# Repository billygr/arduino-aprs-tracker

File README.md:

# arduino-aprs-tracker

Arduino APRS Tracker based on libAPRS with SmartBeaconing

## Hardware
* Arduino Pro Mini 3.3V 8 MHz https://www.adafruit.com/products/2377
* Adafruit Ultimate GPS https://www.adafruit.com/product/746
* or any GPS that can output NMEA (NEO-6M is tested with some minor issues)

## Libraries
* TinyGPS http://arduiniana.org/libraries/tinygps/
* libAPRS (modified) https://github.com/billygr/LibAPRS

## Notes
There are cases where the NEO-6M displays wrong data such as course/altitude. I have trace it to the interrupt of ADC (needed for APRS).
When the interrupt is fired, disrupts the SoftwareSerial so it looses GPS messages.
By default NEO-6M has these messages enabled GSV, RMC, GSA, GGA, GLL, VTG, TXT. 
The GLL is not needed so it is disabled on power on. If you still have issues enable the define, it will switch the NEO-6M on 4800 baud which looks like it fixes it

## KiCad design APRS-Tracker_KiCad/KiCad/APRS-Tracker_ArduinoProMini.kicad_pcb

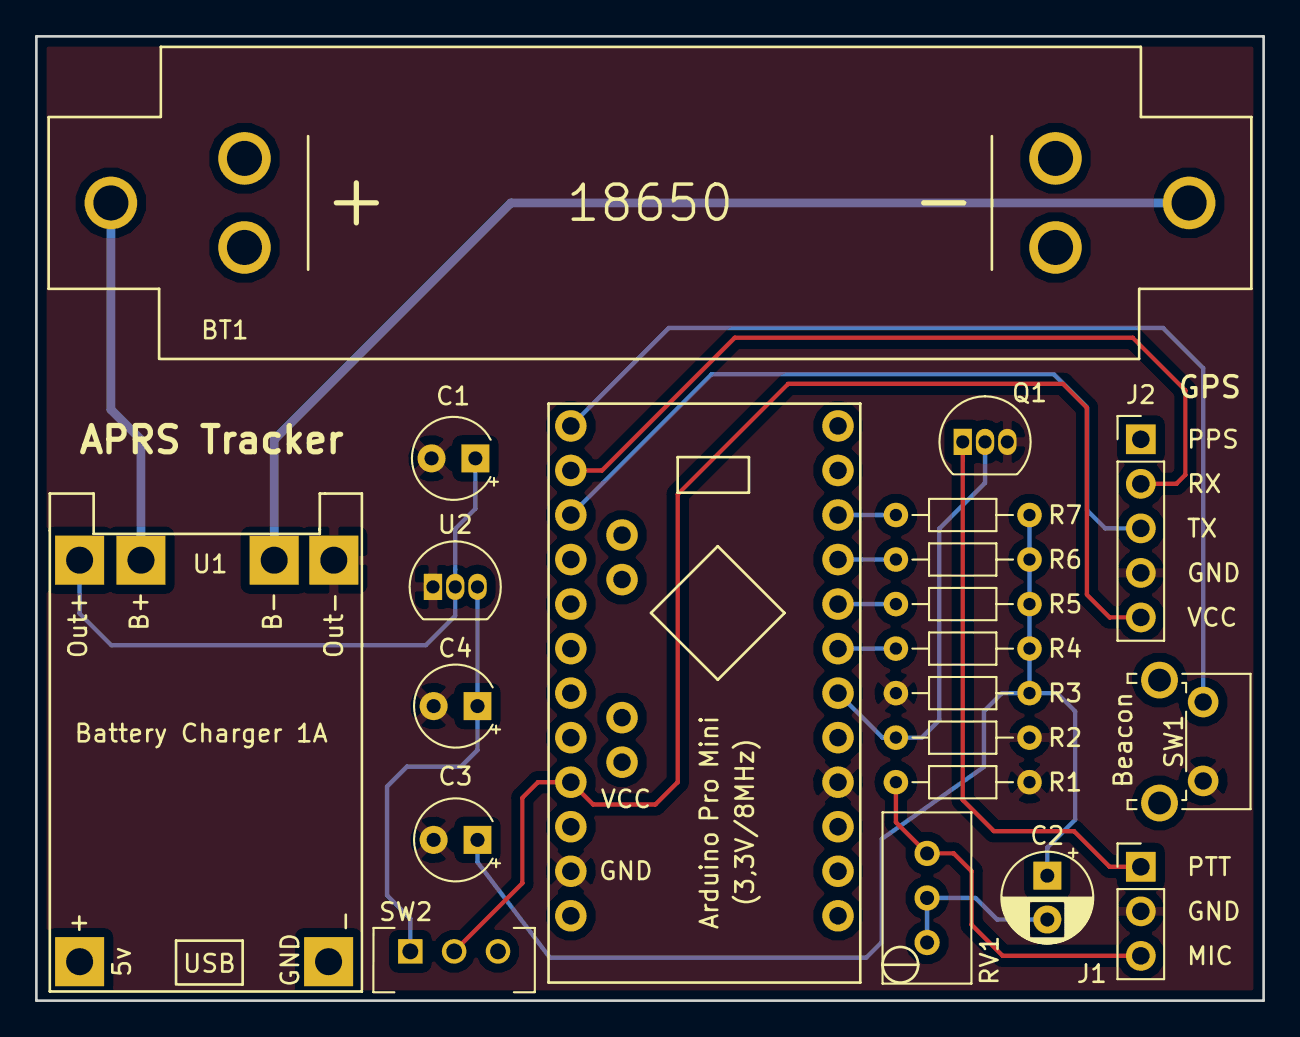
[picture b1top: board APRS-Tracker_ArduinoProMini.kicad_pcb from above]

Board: 2 copper layers, 70.0 x 55.0 mm, 21 parts (0 on the bottom side), 18 nets.

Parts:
BT1: Battery_Cell; Battery_ClipHolder_18650
C1, C4: 1uF; CP_Radial_Tantal_D4.5mm_P2.50mm
C2: 4,7uF/16V; CP_Radial_D5.0mm_P2.50mm
C3: 100nF; CP_Radial_Tantal_D4.5mm_P2.50mm
J1: Conn_01x03_Male; PinHeader_1x03_P2.54mm_Vertical
J2: Conn_01x05_Male; PinHeader_1x05_P2.54mm_Vertical
Q1: BS170; TO-92_Inline
R1, R7: 1k; R_Axial_DIN0204_L3.6mm_D1.6mm_P7.62mm_Horizontal
R2: 10k; R_Axial_DIN0204_L3.6mm_D1.6mm_P7.62mm_Horizontal
R3: 270; R_Axial_DIN0204_L3.6mm_D1.6mm_P7.62mm_Horizontal
R4: 8,2k; R_Axial_DIN0204_L3.6mm_D1.6mm_P7.62mm_Horizontal
R5: 3,9k; R_Axial_DIN0204_L3.6mm_D1.6mm_P7.62mm_Horizontal
R6: 2,2k; R_Axial_DIN0204_L3.6mm_D1.6mm_P7.62mm_Horizontal
RV1: 10k; Potentiometer_Bourns_3296W_Vertical
SW1: SW_Push; SW_Tactile_SPST_Angled_PTS645Vx31-2LFS
SW2: SW_SPDT; SW_CuK_JS202011BQN_SPDT_Angled
U1: TP4056; TP4056-18650
U2: MCP1700-3302E_TO92; TO-92_Inline
U3: Arduino-Pro-Mini; Arduino-ProMini

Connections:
+3V3: J2.5, SW2.2, U3.21
/MIC_ANALOG_OUT: J1.3, R1.2, RV1.3
/PTT: J1.1, Q1.1
/PTT_IN: Q1.2, R2.1, U3.6
/RX: J2.2, U3.14
/TX: J2.3, U3.15
GND: C1.2, C3.2, C4.2, J1.2, J2.4, Q1.3, R1.1, R2.2, R3.1, SW1.2, U1.4, U2.1, U3.4, U3.23
unnamed: BT1.1, U1.5
unnamed: BT1.2, U1.6
unnamed: C1.1, U1.3, U2.2
unnamed: C2.1, C3.1, R3.2, R4.2, R5.2, R6.2, R7.2
unnamed: C2.2, RV1.1, RV1.2
unnamed: C4.1, SW2.1, U2.3
unnamed: R4.1, U3.7
unnamed: R5.1, U3.8
unnamed: R6.1, U3.9
unnamed: R7.1, U3.10
unnamed: SW1.1, U3.13

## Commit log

2016-12-24 Import working version to git
2017-04-03 Fixes aprs conversion for negative lat/long
2017-08-15 Possible fix for wrong APRS icon
2017-11-13 Fix some warnings
2017-12-28 Fix for 3 digit lattitude
2018-07-08 Add configuration for the platformio build system.
2019-04-14 KiCad & Gerber Files for PCB
2019-04-16 Pictures added
2019-04-16 Pic size small
2019-09-19 Moved the ino under a folder to fix issues with travis
2019-12-31 Small updates, doc, indentation
2020-01-05 Fix warnings
    Use %lu for unsigned long variables.
2020-01-12 Added GPS fix led on A3 pin
2020-01-12 Added the SimpleTimer to the project from commit b30890b8f7046bf3b0258e5870e5dda78ac5c71a since the Arduino Library manager contains a complete different project/version
2020-01-12 Use the buidin SimpleTimer
2020-04-20 Added altitude in comment section of APRS messsage
2020-04-20 fix typo
2020-04-20 ... hopefully right this time
2020-04-20 fixing the buffer overflow...
2020-04-20 Fixing APRS message
2020-07-21 implement smartbeaconing
2020-07-26 Small cleanup and adapt to my hardware
2021-01-25 Potential fix for 0 on lat
2021-01-27 Reduce memory usage on 1.8.13
    Sketch uses 16616 bytes (54%) of program storage space. Maximum is 30720 bytes.
    Global variables use 1274 bytes (62%) of dynamic memory, leaving 774 bytes for local variables. Maximum is 2048 bytes.
    Sketch uses 16368 bytes (53%) of program storage space. Maximum is 30720 bytes.
    Global variables use 1243 bytes (60%) of dynamic memory, leaving 805 bytes for local variables. Maximum is 2048 bytes.
2022-02-27 Added debug for smartbeaconing updates
2022-02-27 Possible fix for wrong course data
2022-02-27 Fix the usual equal test...
2022-02-27 Fix eventually the multiple updates
2022-02-28 Changes for vscode
2022-03-02 Major rewrite using TinyGPS code, a bit bigger in memory but more clean
2022-03-02 More checks for valid data
2022-03-05 Catch the issue with the ADC interrupt killing the SoftSerial for NEO-6M
2022-03-05 Disable GPGLL
2024-03-24 Converted to Kicad 7.x changed designators
2024-03-24 New file format
2024-03-24 Fixing directory structure
2024-03-24 Moved the Kicad 5.x version to archive
2024-03-24 Added the missing PCBv1 Kicad files
2024-03-24 Fix warning
2024-03-24 Added fix LED
